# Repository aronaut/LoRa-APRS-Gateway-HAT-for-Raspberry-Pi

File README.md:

What is it?
-----------
With this LoRa APRS board you can build a LoRa APRS single channel Gateway.  
The Board is based on the development of https://www.lora-aprs.at/ and http://www.iot4pi.com/  
It works with a Raspberry Pi (2 Model B, 3 Model B an B+, Zero WH).  
Power is provided by Raspberry Pi.

What you find here
------------------
- KiCad Fils
- Gerber Files
- Manuals
- Pictures of the LoRa-APRS-Board

Info & Software
---------------
You find information and Software for the LoRa-APRS Gateway at  
https://www.aronaut.at/2019/11/lora-aprs-gateway-fur-raspberry-pi/  
https://www.lora-aprs.at/  
http://www.iot4pi.com/de/hardware/lora-gateway/  
https://github.com/tomelec/RPi-LoRa-KISS-TNC

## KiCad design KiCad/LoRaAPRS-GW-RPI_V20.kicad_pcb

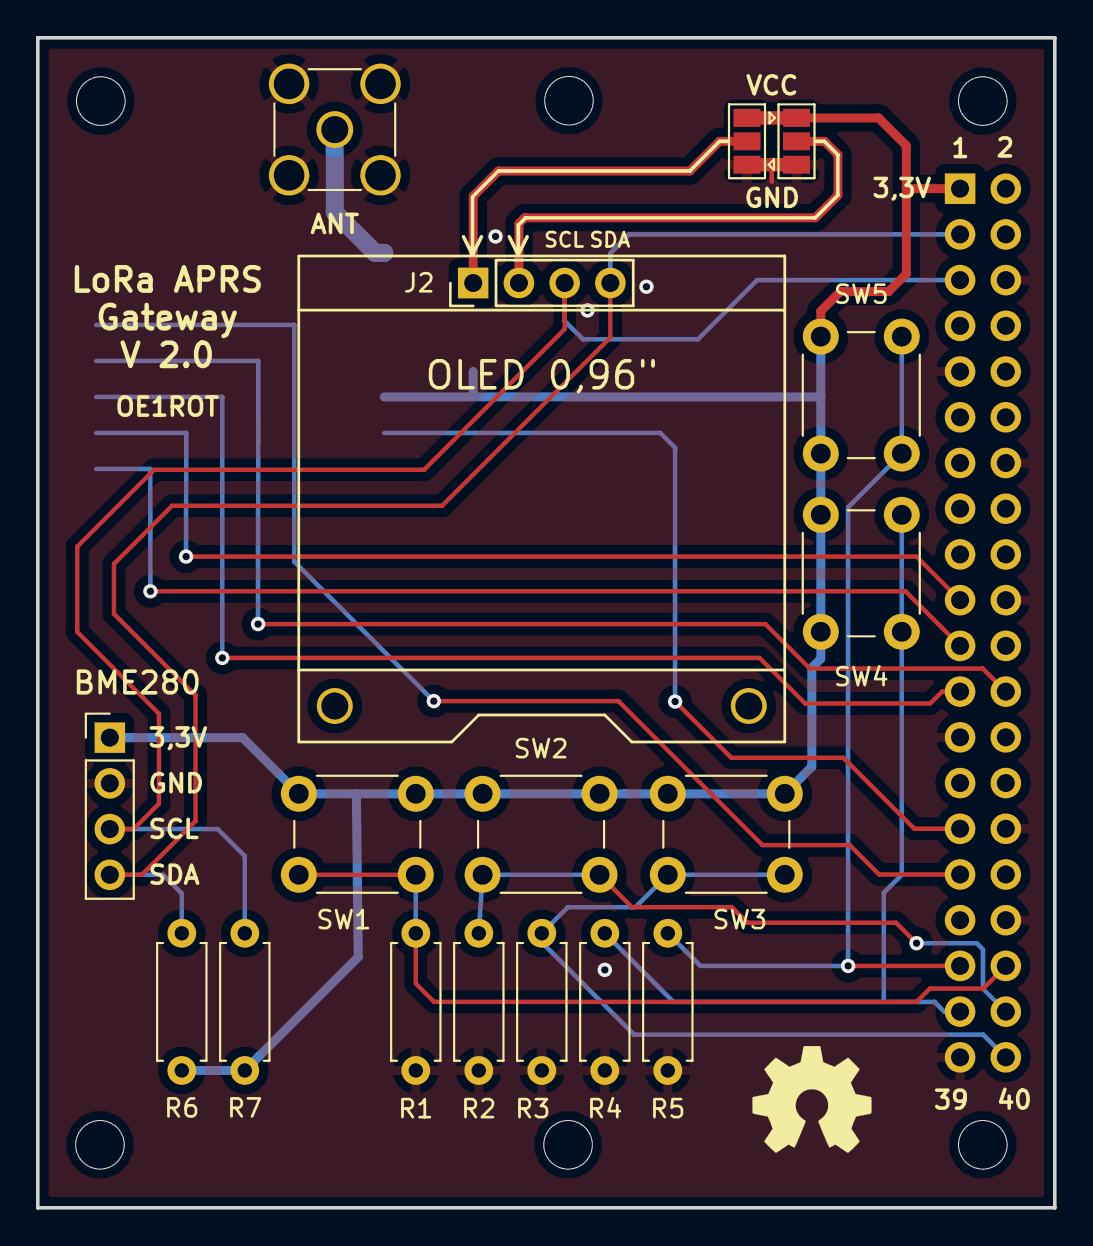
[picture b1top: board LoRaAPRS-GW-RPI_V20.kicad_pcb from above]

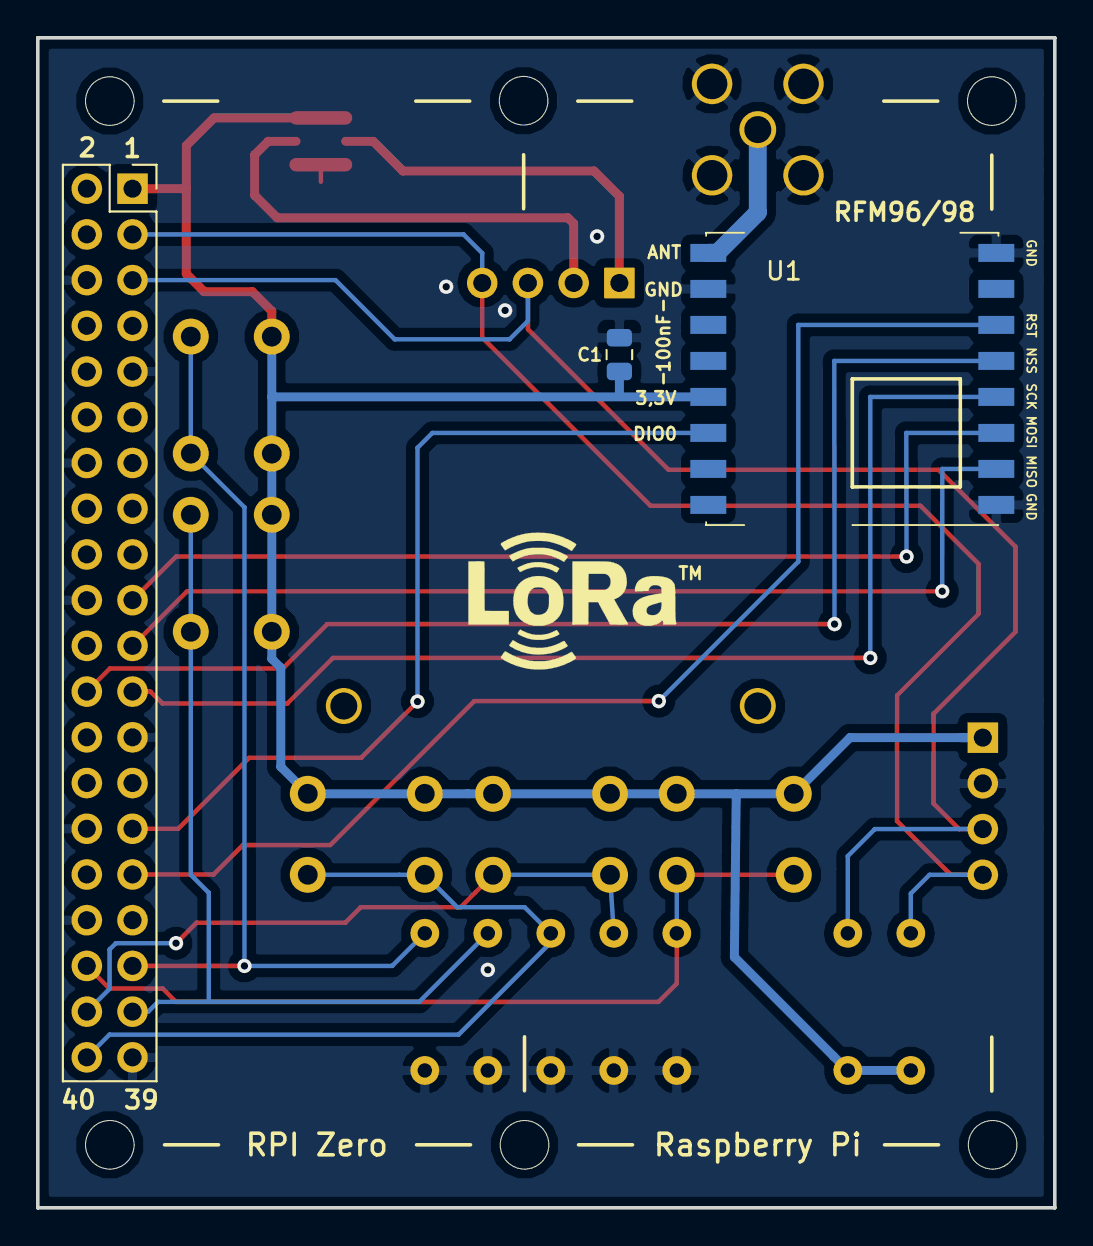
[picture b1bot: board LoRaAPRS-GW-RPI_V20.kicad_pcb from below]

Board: 2 copper layers, 56.5 x 65.0 mm, 20 parts (3 on the bottom side), 18 nets.

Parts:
AE1: Antenna_Shield; SMA_Amphenol_901-144_Vertical
C1: C; C_0805_2012Metric
J1: Raspberry PI Header; PinSocket_2x20_P2.54mm_Vertical
J2: Display; OLED_0,96_II
J3: BME280; PinHeader_1x04_P2.54mm_Vertical
JP1, JP2: SolderJumper_3_Open; SolderJumper-3_P1.3mm_Open_Pad1.0x1.5mm
R1, R2, R3, R4, R5: 47k; R_Axial_DIN0207_L6.3mm_D2.5mm_P7.62mm_Horizontal
R6, R7: 10k; R_Axial_DIN0207_L6.3mm_D2.5mm_P7.62mm_Horizontal
SW1, SW2, SW3, SW4, SW5: SW_Push; SW_PUSH_6mm_H5mm
U1: RFM96W-433S2; HOPERF_RFM9XW_SMD

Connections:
+3V3: C1.1, J1.1, J3.1, JP1.3, JP2.1, R6.1, R7.1, SW1.1, SW2.1, SW3.1, SW4.1, SW5.1, U1.13
D1: J2.1, JP1.2
D2: J2.2, JP2.2
DIO0: J1.29, U1.14
DOWN: J1.37, R4.1, SW4.2
GND: AE1.2, C1.2, J1.6, J1.9, J1.14, J1.20, J1.25, J1.30, J1.34, J1.39, J3.2, JP1.1, JP2.3, R1.2, R2.2, R3.2, R4.2, R5.2, U1.1, U1.8, U1.10
MISO: J1.21, U1.2
MOSI: J1.19, U1.3
NSS: J1.24, U1.5
unnamed: AE1.1, U1.9
Reset: J1.31, U1.6
SCK: J1.23, U1.4
SCL: J1.5, J2.3, J3.3, R7.2
SDA: J1.3, J2.4, J3.4, R6.2
T1: J1.36, R1.1, SW1.2
T2: J1.38, R2.1, SW2.2
T3: J1.40, R3.1, SW3.2
UP: J1.35, R5.1, SW5.2

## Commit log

2020-04-26 LoRa APRS GW V2.0 BME280
2020-04-26 README.md
